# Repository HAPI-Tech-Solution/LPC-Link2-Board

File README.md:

# LPC-Link2-Board
First Crea
LPCLink2の信号を外に引き出す為のブレークアウトボードです。
ハーフピッチコネクタは秋葉原界隈で売っているロングタイプを代用するか専用タイプを実装するか選べます。
表面実装タイプです。

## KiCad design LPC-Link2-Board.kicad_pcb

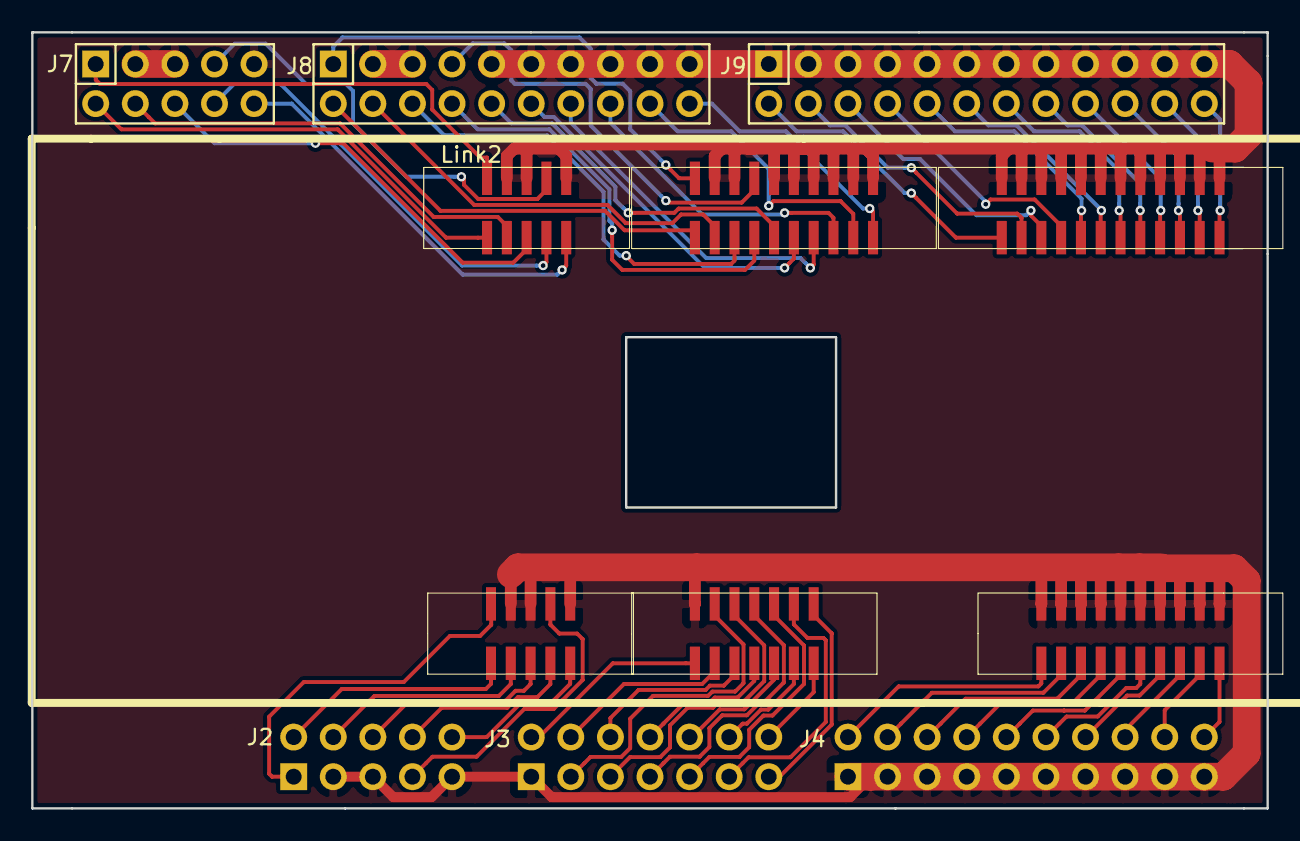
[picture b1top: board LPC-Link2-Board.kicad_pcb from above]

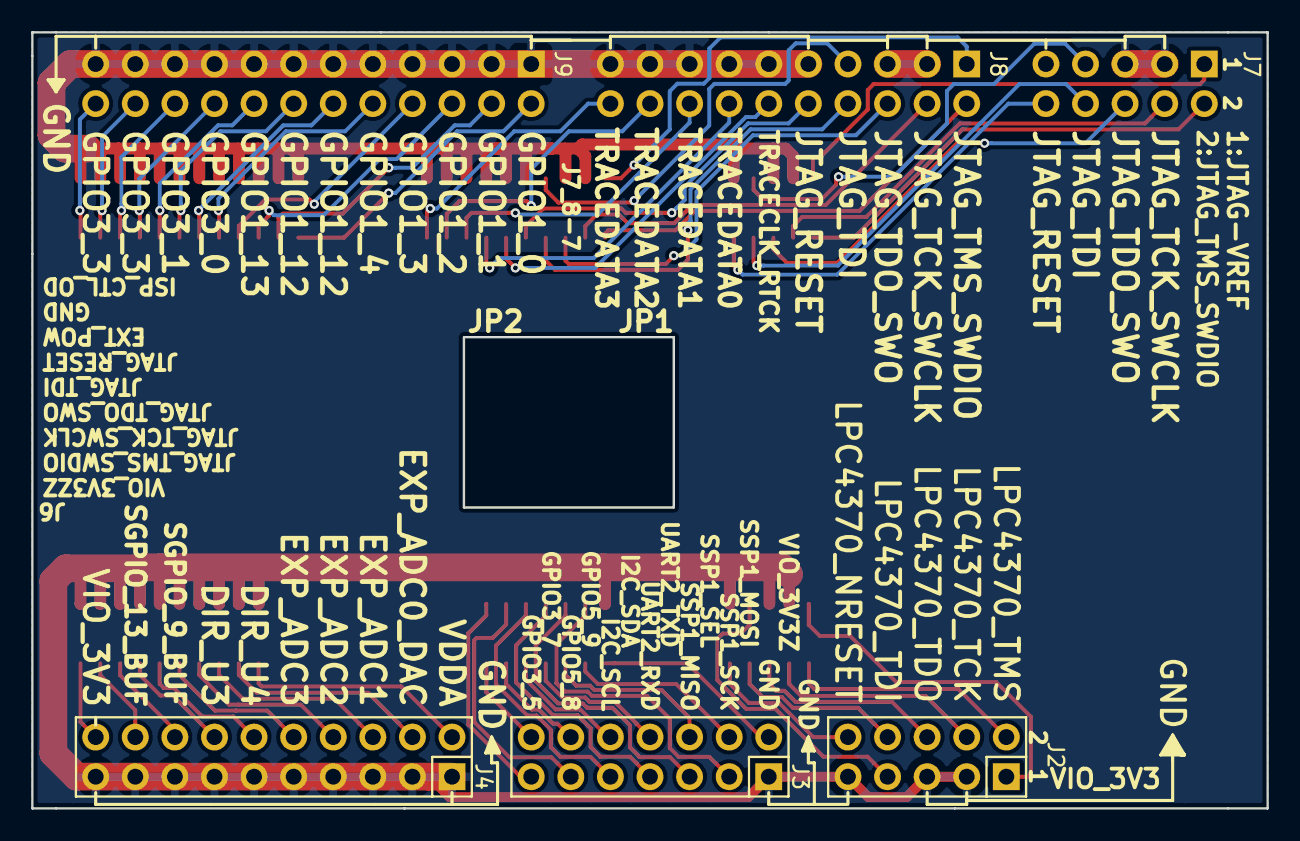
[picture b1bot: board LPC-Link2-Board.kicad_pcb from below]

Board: 2 copper layers, 79.2 x 49.8 mm, 7 parts (3 on the bottom side), 62 nets.

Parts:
J2, J7: CONN_02X05; Socket_Strip_Straight_2x05
J3: CONN_02X07; Socket_Strip_Straight_2x07
J4, J8: CONN_02X10; Socket_Strip_Straight_2x10
J9: CONN_02X12; Socket_Strip_Straight_2x12
Link2: LPCLink2; LPCLink2_Base-SMT

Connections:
GND: J2.3, J2.5, J2.9, J3.1, J4.1, J4.3, J4.5, J4.7, J4.9, J4.11, J4.13, J4.15, J4.17, J4.19, J7.3, J7.5, J7.9, J8.3, J8.5, J8.9, J8.11, J8.13, J8.15, J8.17, J8.19, J9.1, J9.3, J9.5, J9.7, J9.9, J9.11, J9.13, J9.15, J9.17, J9.19, J9.21, J9.23, Link2.2-3, Link2.2-5, Link2.2-9, Link2.3-1, Link2.4-1, Link2.4-3, Link2.4-5, Link2.4-7, Link2.4-9, Link2.4-11, Link2.4-13, Link2.4-15, Link2.4-17, Link2.4-19, Link2.7-3, Link2.7-5, Link2.7-9, Link2.8-3, Link2.8-5, Link2.8-9, Link2.8-11, Link2.8-13, Link2.8-15, Link2.8-17, Link2.8-19, Link2.9-1, Link2.9-3, Link2.9-5, Link2.9-7, Link2.9-9, Link2.9-11, Link2.9-13, Link2.9-15, Link2.9-17, Link2.9-19, Link2.9-21, Link2.9-23
unnamed: J2.1, Link2.2-1
unnamed: J2.2, Link2.2-2
unnamed: J2.4, Link2.2-4
unnamed: J2.6, Link2.2-6
unnamed: J2.7, Link2.2-7
unnamed: J2.8, Link2.2-8
unnamed: J2.10, Link2.2-10
unnamed: J3.2, Link2.3-2
unnamed: J3.3, Link2.3-3
unnamed: J3.4, Link2.3-4
unnamed: J3.5, Link2.3-5
unnamed: J3.6, Link2.3-6
unnamed: J3.7, Link2.3-7
unnamed: J3.8, Link2.3-8
unnamed: J3.9, Link2.3-9
unnamed: J3.10, Link2.3-10
unnamed: J3.11, Link2.3-11
unnamed: J3.12, Link2.3-12
unnamed: J3.13, Link2.3-13
unnamed: J3.14, Link2.3-14
unnamed: J4.2, Link2.4-2
unnamed: J4.4, Link2.4-4
unnamed: J4.6, Link2.4-6
unnamed: J4.8, Link2.4-8
unnamed: J4.10, Link2.4-10
unnamed: J4.12, Link2.4-12
unnamed: J4.14, Link2.4-14
unnamed: J4.16, Link2.4-16
unnamed: J4.18, Link2.4-18
unnamed: J4.20, Link2.4-20
unnamed: J7.1, Link2.7-1
unnamed: J7.2, Link2.7-2
unnamed: J7.4, Link2.7-4
unnamed: J7.6, Link2.7-6
unnamed: J7.7, Link2.7-7
unnamed: J7.8, Link2.7-8
unnamed: J7.10, Link2.7-10
unnamed: J8.1, Link2.8-1
unnamed: J8.2, Link2.8-2
unnamed: J8.4, Link2.8-4
unnamed: J8.6, Link2.8-6
unnamed: J8.7, Link2.8-7
unnamed: J8.8, Link2.8-8
unnamed: J8.10, Link2.8-10
unnamed: J8.12, Link2.8-12
unnamed: J8.14, Link2.8-14
unnamed: J8.16, Link2.8-16
unnamed: J8.18, Link2.8-18
unnamed: J8.20, Link2.8-20
unnamed: J9.2, Link2.9-2
unnamed: J9.4, Link2.9-4
unnamed: J9.6, Link2.9-6
unnamed: J9.8, Link2.9-8
unnamed: J9.10, Link2.9-10
unnamed: J9.12, Link2.9-12
unnamed: J9.14, Link2.9-14
unnamed: J9.16, Link2.9-16
unnamed: J9.18, Link2.9-18
unnamed: J9.20, Link2.9-20
unnamed: J9.22, Link2.9-22
unnamed: J9.24, Link2.9-24

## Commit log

2015-07-10 First Create
2015-07-12 no message
